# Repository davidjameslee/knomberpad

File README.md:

# KnomberPad

Custom numberpad peripheral

## TODOS
* Mounting holes
* Versioning/Branding
* Encoder button? (Different foot print)
* Convert to through hole diodes

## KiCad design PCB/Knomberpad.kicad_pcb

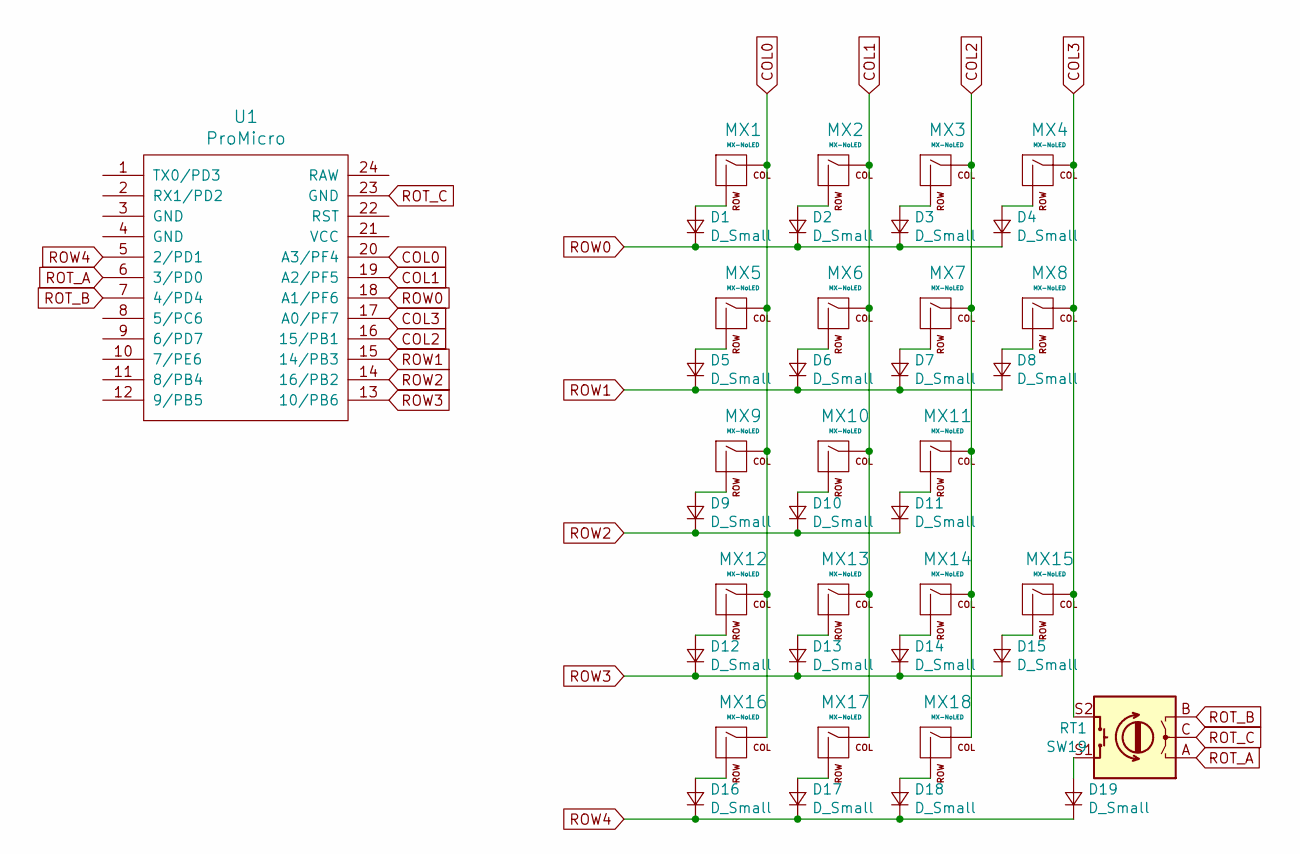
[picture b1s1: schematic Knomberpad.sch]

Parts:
D1, D2, D3, D4, D5, D6, D7, D8, D9, D10, D11, D12, D13, D14, D15, D16, D17, D18, D19: D_Small; Diode; LCSC C81598
MX1, MX2, MX3, MX4, MX5, MX6, MX7, MX9, MX10, MX11, MX12, MX13, MX14, MX16, MX17, MX18: MX-NoLED; MX-1U-NoLED
MX8, MX15: MX-NoLED; MX-2U-NoLED
SW19: RT1; RotaryEncoder_EC11
U1: ProMicro; ArduinoProMicro-ZigZag

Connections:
COL0: MX1.1 (COL), MX5.1 (COL), MX9.1 (COL), MX12.1 (COL), MX16.1 (COL), U1.20 (A3/PF4)
COL1: MX2.1 (COL), MX6.1 (COL), MX10.1 (COL), MX13.1 (COL), MX17.1 (COL), U1.19 (A2/PF5)
COL2: MX3.1 (COL), MX7.1 (COL), MX11.1 (COL), MX14.1 (COL), MX18.1 (COL), U1.16 (15/PB1)
COL3: MX4.1 (COL), MX8.1 (COL), MX15.1 (COL), SW19.S2, U1.17 (A0/PF7)
unnamed: D1.2 (A), MX1.2 (ROW)
unnamed: D2.2 (A), MX2.2 (ROW)
unnamed: D3.2 (A), MX3.2 (ROW)
unnamed: D4.2 (A), MX4.2 (ROW)
unnamed: D5.2 (A), MX5.2 (ROW)
unnamed: D6.2 (A), MX6.2 (ROW)
unnamed: D7.2 (A), MX7.2 (ROW)
unnamed: D8.2 (A), MX8.2 (ROW)
unnamed: D9.2 (A), MX9.2 (ROW)
unnamed: D10.2 (A), MX10.2 (ROW)
unnamed: D11.2 (A), MX11.2 (ROW)
unnamed: D12.2 (A), MX12.2 (ROW)
unnamed: D13.2 (A), MX13.2 (ROW)
unnamed: D14.2 (A), MX14.2 (ROW)
unnamed: D15.2 (A), MX15.2 (ROW)
unnamed: D16.2 (A), MX16.2 (ROW)
unnamed: D17.2 (A), MX17.2 (ROW)
unnamed: D18.2 (A), MX18.2 (ROW)
unnamed: D19.2 (A), SW19.S1
ROT_A: SW19.A, U1.6 (3/PD0)
ROT_B: SW19.B, U1.7 (4/PD4)
ROT_C: SW19.C, U1.23 (GND)
ROW0: D1.1 (K), D2.1 (K), D3.1 (K), D4.1 (K), U1.18 (A1/PF6)
ROW1: D5.1 (K), D6.1 (K), D7.1 (K), D8.1 (K), U1.15 (14/PB3)
ROW2: D9.1 (K), D10.1 (K), D11.1 (K), U1.14 (16/PB2)
ROW3: D12.1 (K), D13.1 (K), D14.1 (K), D15.1 (K), U1.13 (10/PB6)
ROW4: D16.1 (K), D17.1 (K), D18.1 (K), D19.1 (K), U1.5 (2/PD1)

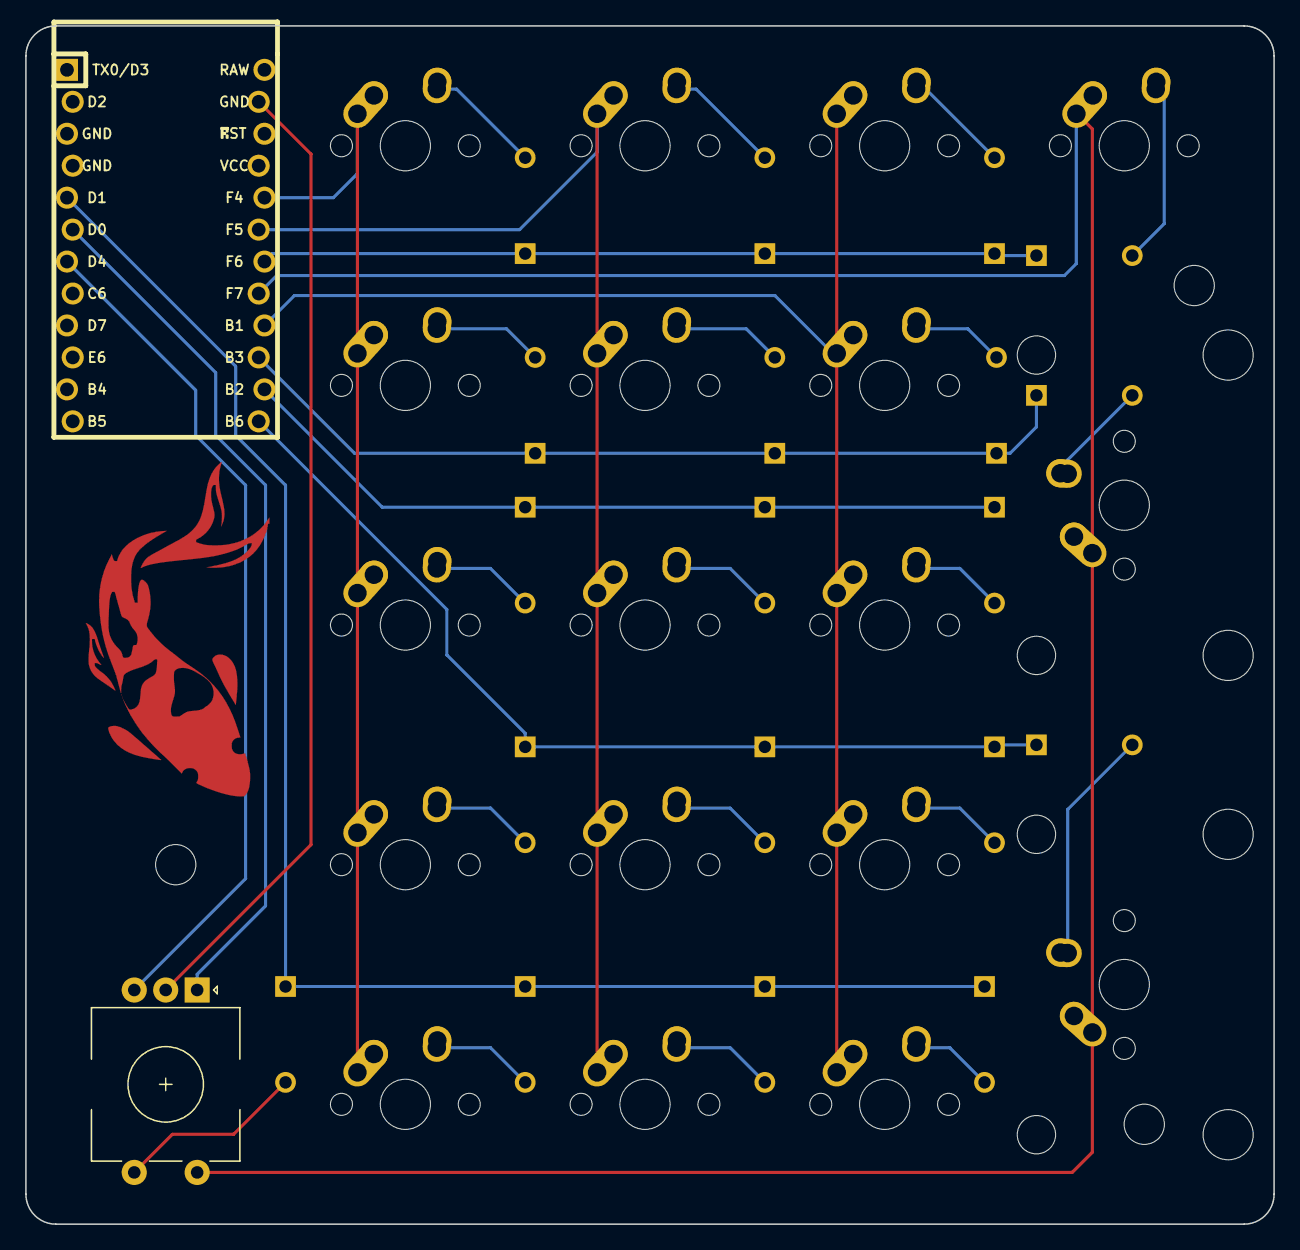
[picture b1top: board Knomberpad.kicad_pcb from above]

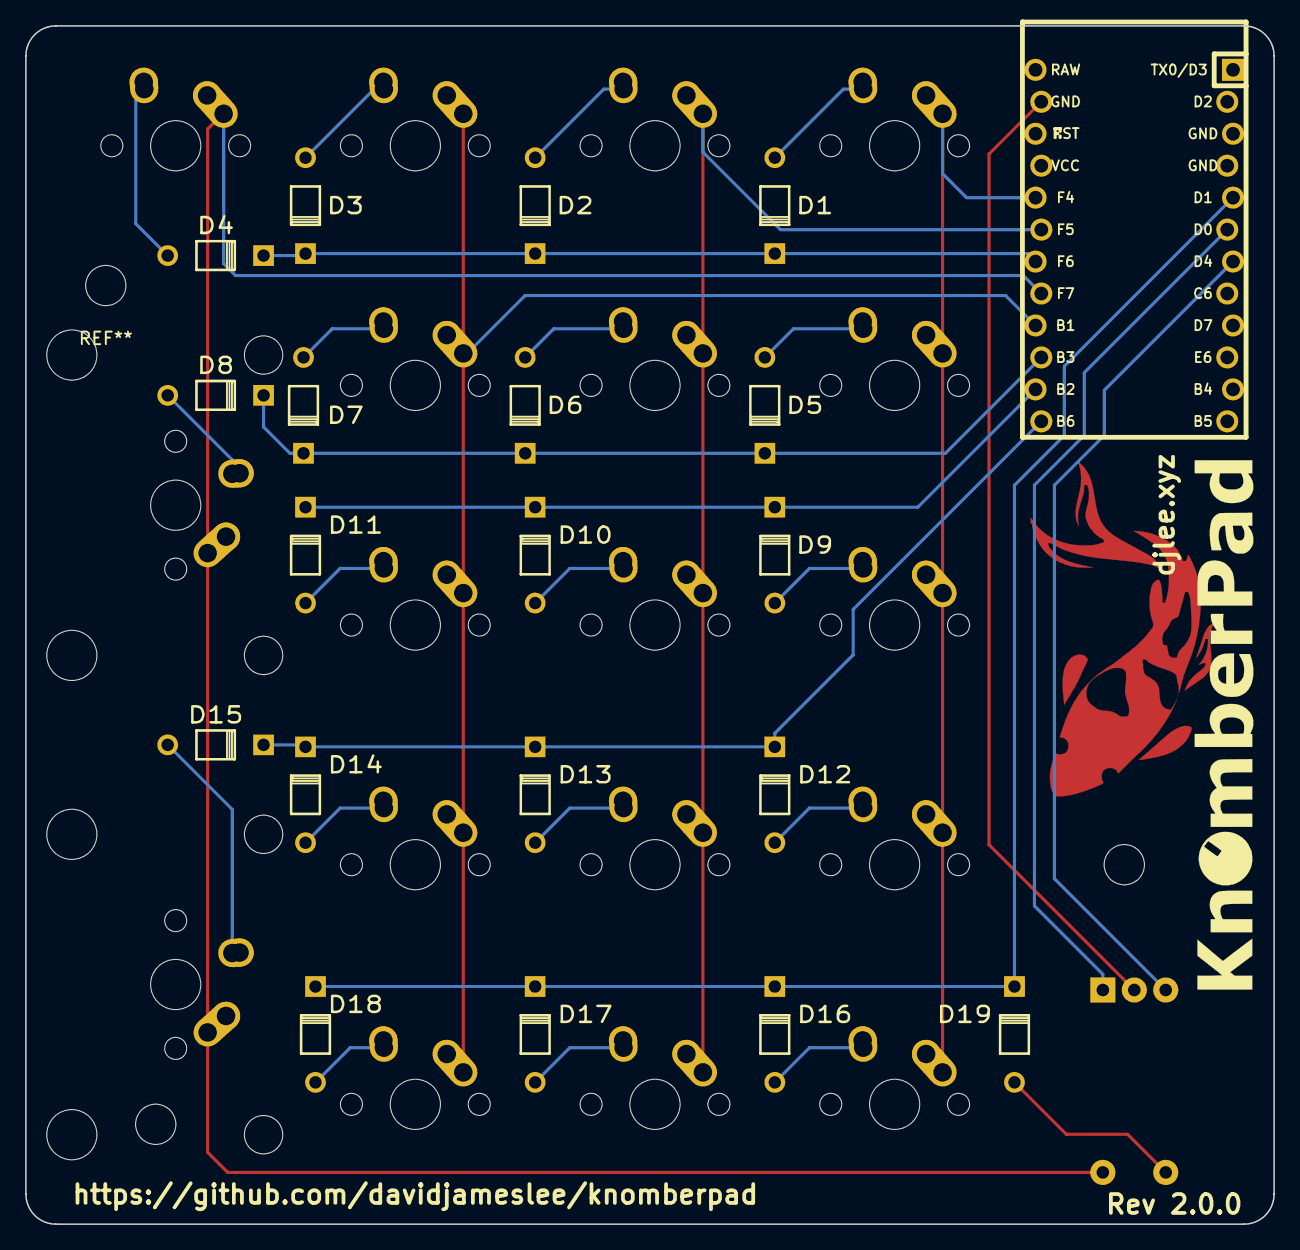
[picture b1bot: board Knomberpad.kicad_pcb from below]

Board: 2 copper layers, 99.2 x 95.3 mm, 41 parts (21 on the bottom side), 31 nets.

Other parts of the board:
 : MountingHole_3.2mm_M3
 #2: MountingHole_3.2mm_M3

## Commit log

2020-11-19 First attempt
2020-11-19 fix readme.md
2020-11-20 fix name...
2020-11-22 Change footprints
2020-12-03 add branding and gerbers
